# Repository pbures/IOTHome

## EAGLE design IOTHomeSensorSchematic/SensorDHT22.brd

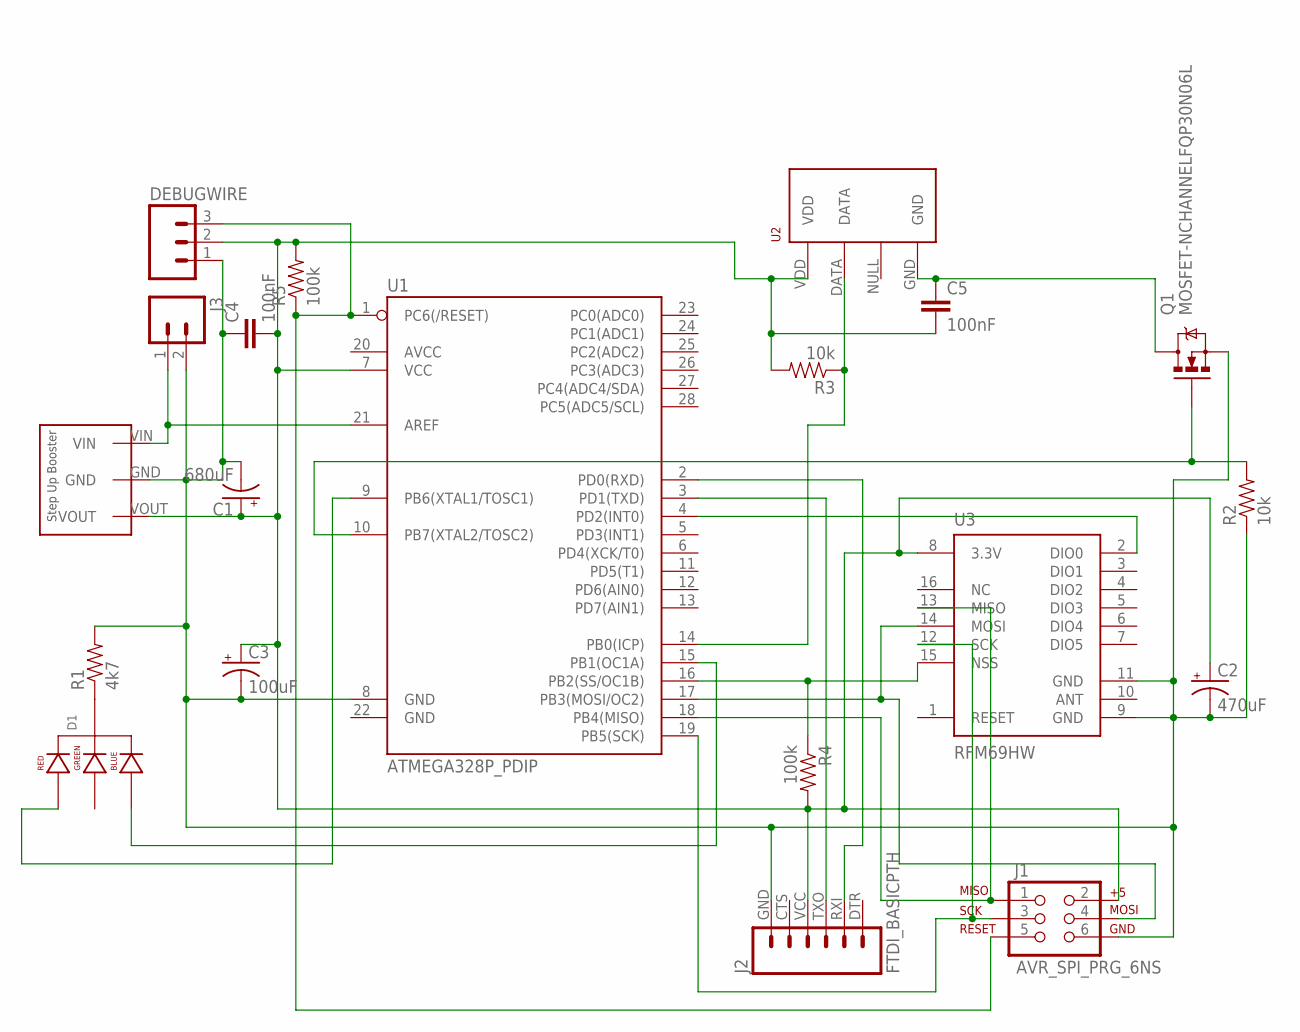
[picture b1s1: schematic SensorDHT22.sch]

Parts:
C1: 680uF; CPOL-RADIAL-100UF-25V
C2: 470uF; CPOL-RADIAL-100UF-25V
C3: 100uF; CPOL-RADIAL-10UF-25V
C4, C5: 100nF; CAP-PTH-SMALL
D1: LED-RGB-CC-THRUCLEAR; LED-RGB-THRU
DEBUGWIRE: M03PTH; 1X03
J1: AVR_SPI_PRG_6NS; 2X3-NS
J2: FTDI_BASICPTH; FTDI_BASIC
J3: M02POLAR; MOLEX-1X2
Q1: MOSFET-NCHANNELFQP30N06L; TO220V
R1: 4k7; AXIAL-0.4
R2, R3: 10k; AXIAL-0.3
R4: 100k; AXIAL-0.4
R5: 100k; AXIAL-0.3
STEPUP: POLOLU-2563
U1: ATMEGA328P_PDIP; DIL28-3
U2: RHT03_DHT-22_AM2302; RHT03_DHT-22
U3: RFM69HW; RFM69W-XXXS2

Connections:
unnamed: C1.2 (-), C2.2 (-), C3.2 (-), C4.1, DEBUGWIRE.1, J1.6, J2.GND (6), J3.2, Q1.3 (S), R1.P$2 (2), R2.P$1 (1), STEPUP.GND, U1.8 (GND), U3.9 (GND), U3.11 (GND)
unnamed: J3.1, STEPUP.VIN, U1.21 (AREF)
unnamed: C5.1, Q1.2 (D), U2.GND
unnamed: J2.TXO (3), U1.3 (PD1(TXD))
unnamed: R4.P$1 (1), U1.16 (PB2(SS/OC1B)), U3.15 (NSS)
unnamed: Q1.1 (G), R2.P$2 (2), U1.10 (PB7(XTAL2/TOSC2))
unnamed: J2.RXI (2), U1.2 (PD0(RXD))
unnamed: U1.4 (PD2(INT0)), U3.2 (DIO0)
unnamed: R3.P$1 (1), U1.14 (PB0(ICP)), U2.DATA
unnamed: D1.4 (BLUE_CATHODE), U1.15 (PB1(OC1A))
unnamed: D1.1 (RED_CATHODE), U1.9 (PB6(XTAL1/TOSC1))
unnamed: D1.2 (CATHODE), R1.P$1 (1)
unnamed: J1.4, U1.17 (PB3(MOSI/OC2)), U3.14 (MOSI)
unnamed: J1.1, U1.18 (PB4(MISO)), U3.13 (MISO)
unnamed: DEBUGWIRE.3, J1.5, R5.P$1 (1), U1.1 (PC6(/RESET))
unnamed: C1.1 (+), C2.1 (+), C3.1 (+), C4.2, C5.2, DEBUGWIRE.2, J1.2, J2.VCC (4), R3.P$2 (2), R4.P$2 (2), R5.P$2 (2), STEPUP.VOUT, U1.7 (VCC), U2.VDD, U3.8 (3.3V)
unnamed: J1.3, U1.19 (PB5(SCK)), U3.12 (SCK)

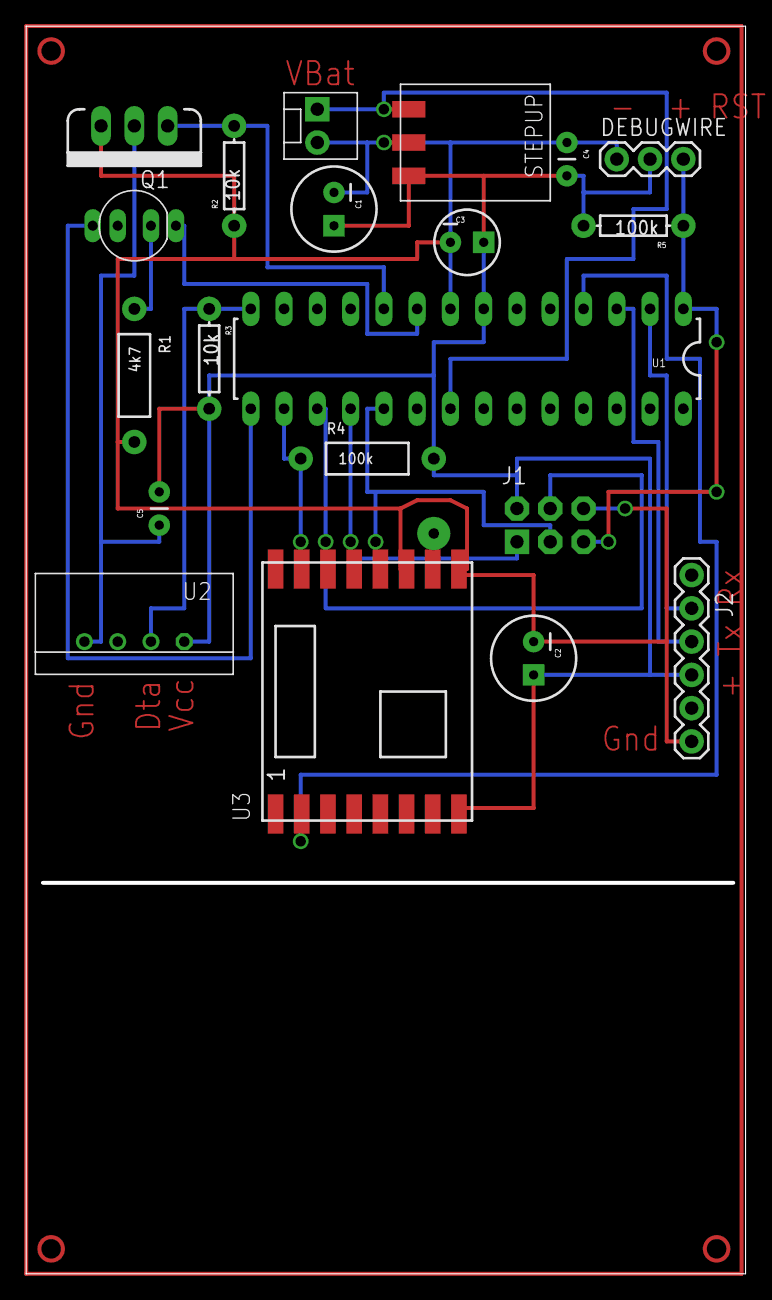
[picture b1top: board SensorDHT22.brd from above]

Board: 2 copper layers, 54.6 x 94.9 mm, 20 parts (0 on the bottom side), 17 nets.

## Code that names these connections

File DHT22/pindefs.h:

#ifndef PINDEFS_H_
#define PINDEFS_H_

#define SET_INPUT_MODE(ddr,bit) ddr &= ~(1<<bit)
#define SET_OUTPUT_MODE(ddr,bit) ddr |= (1<<bit)

#define SET_HIGH(port,bit) port |= (1<<bit)
#define SET_LOW(port,bit) port &= ~(1<<bit)

#define BLINK(port,bit) SET_HIGH(port,bit);SET_LOW(port,bit);
#define BLINK_DELAY(port,bit,ms) SET_HIGH(port,bit);_delay_ms(ms);SET_LOW(port,bit);

#define SET_HIGH_REF(port,bit) *port |= (1<<bit)
#define SET_LOW_REF(port,bit) *port &= ~(1<<bit)

/* RF69 Definition */
#define RF69_SPI_CS_DDR    DDRB
#define RF69_SPI_CS_PORT   PORTB
#define RF69_SPI_CS_PIN    PINB
#define RF69_SPI_CS_BIT    PB2

#define RF69_DIO0_DDR  DDRD
#define RF69_DIO0_PORT PORTD
#define RF69_DIO0_PIN  PIND
#define RF69_DIO0_BIT  PD2

/* DHT22 Sensor data */
#define DHT22_DDR DDRB
#define DHT22_PORT PORTB
#define DHT22_PIN PINB
#define DHT22_BIT PB0

/* Pin the control LED */
#define LED_DDR 	DDRB
#define LED_PORT 	PORTB
#define LED_PIN 	PINB
#define LED_BIT 	PB1

#define SPI_SS_DDR  DDRB
#define SPI_SS_PORT PORTB
#define SPI_SS_PIN  PINB
#define SPI_SS_BIT  PB6



#define I2C_SDA        PC4
#define I2C_SDA_PORT   PORTC
#define I2C_SDA_PIN    PINC
#define I2C_SDA_DDR    DDRC

#define I2C_SCL        PC5
#define I2C_SCL_PORT   PORTC
#define I2C_SCL_PIN    PINC
#define I2C_SCL_DDR    DDRC

#endif /* PINDEFS_H_ */

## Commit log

2017-02-23 Initial code commit
2017-02-25 Battery indicator implemented
2017-03-08 Schematic, board creation
2017-03-14 Added schematic PCB design

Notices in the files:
parts and their libraries:
SparkFun-LED: Licensing: Creative Commons ShareAlike 4.0 International - https://creativecommons.org/licenses/by-sa/4.0
